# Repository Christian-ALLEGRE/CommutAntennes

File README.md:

# CommutAntennes
Antennas switcher using RPIPico and TFT 2"8 TouchScreen

V1.2 : 
  - The TFT 2"8 TouchScreen uses parallel 8 bits communication with RpiPico
  - PCB was manufactured by JLCPcb using Kicad/Ampli144MHz.zip (2023/09/14)
  - RpiPico Program V1.2 UI was design to manage :
    - The antenna switcher : 2 coax relay (HF and VHF)
    - A futur 144MHz 500W Power amplifier (not yet build at this time)
  
Updated on 29/12/2023 : 
  - The source code is now compatible with PlatformIO
    - CommutAntenneRpiPico-V1.2a.ino becomes src/main.cpp
    - The requested libraries were put in lib directory
    - a few lines where commented in GFX_Library_for_Arduino and TouchScreenOnRpPico
      to allow those libraries to compile (search for// F4LAA comment to find them)

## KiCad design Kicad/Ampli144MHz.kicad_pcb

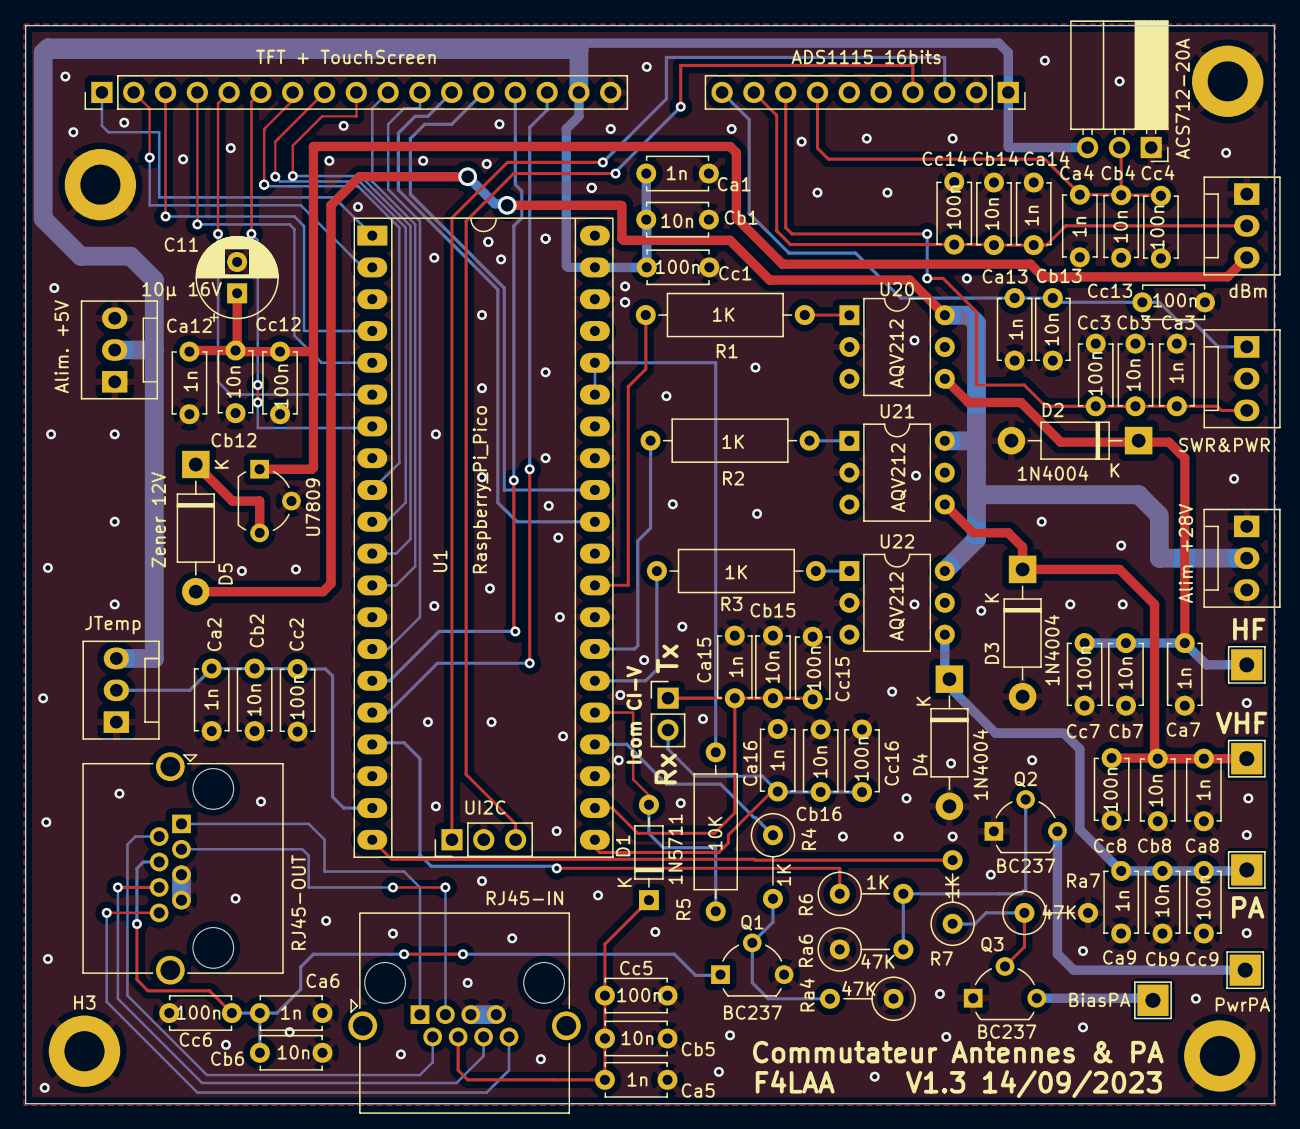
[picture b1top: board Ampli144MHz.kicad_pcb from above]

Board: 2 copper layers, 99.7 x 86.1 mm, 87 parts (0 on the bottom side), 37 nets.

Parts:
Alim +28V: Alim28V; FanPinHeader_1x03_P2.54mm_Vertical
C11: 10µ 16V; CP_Radial_D6.3mm_P2.50mm
CK1: RELAY_K1; TestPoint_THTPad_2.5x2.5mm_Drill1.2mm
CK2: RELAY_K2; TestPoint_THTPad_2.5x2.5mm_Drill1.2mm
CK3: RELAY_K3; TestPoint_THTPad_2.5x2.5mm_Drill1.2mm
CK220V: Alim 48V PA; TestPoint_THTPad_2.5x2.5mm_Drill1.2mm
CKBias1: BiasPA; TestPoint_THTPad_2.5x2.5mm_Drill1.2mm
Ca1, Ca2, Ca3, Ca4, Ca5, Ca6, Ca7, Ca8, Ca9, Ca12, Ca13, Ca14, Ca15, Ca16: 1n; C_Disc_D4.7mm_W2.5mm_P5.00mm
Cb1, Cb2, Cb3, Cb4, Cb5, Cb6, Cb7, Cb8, Cb9, Cb12, Cb13, Cb14, Cb15, Cb16: 10n; C_Disc_D4.7mm_W2.5mm_P5.00mm
Cc1, Cc2, Cc3, Cc4, Cc5, Cc6, Cc7, Cc8, Cc9, Cc12, Cc13, Cc14, Cc15, Cc16: 100n; C_Disc_D4.7mm_W2.5mm_P5.00mm
D1: 1N5711; D_DO-35_SOD27_P7.62mm_Horizontal
D2, D3, D4: 1N4004; D_DO-41_SOD81_P10.16mm_Horizontal
D5: Zener 12V; D_DO-41_SOD81_P10.16mm_Horizontal
H1, H2, H3, H4: MountingHole_Pad; MountingHole_3.2mm_M3_ISO7380_Pad
J5: Alim. +5V; FanPinHeader_1x03_P2.54mm_Vertical
JADC16bits: ADS1115 16bits; PinSocket_1x10_P2.54mm_Vertical
JAmp: ACS712-20A; PinSocket_1x03_P2.54mm_Horizontal
JCIV1: Icom CI-V; PinHeader_1x02_P2.54mm_Vertical
JS+P: SWR&PWR; FanPinHeader_1x03_P2.54mm_Vertical
JTFT+Touch: TFT + TouchScreen; PinHeader_1x17_P2.54mm_Vertical
JTemp: Temp; FanPinHeader_1x03_P2.54mm_Vertical
JdBm: dBm; FanPinHeader_1x03_P2.54mm_Vertical
Q1, Q2, Q3: BC237; TO-92L_Wide
R1, R2, R3: 1K; R_Axial_DIN0309_L9.0mm_D3.2mm_P12.70mm_Horizontal
R4, R6, R7: 1K; R_Axial_DIN0309_L9.0mm_D3.2mm_P5.08mm_Vertical
R5: 10K; R_Axial_DIN0309_L9.0mm_D3.2mm_P12.70mm_Horizontal
RJ45-IN, RJ45-OUT: RJ45_Amphenol_RJHSE5380
Ra4, Ra6, Ra7: 47K; R_Axial_DIN0309_L9.0mm_D3.2mm_P5.08mm_Vertical
U1: Raspberry_Pi_Pico; DIP-40_0.700in_Socket_LongPads
U20, U21, U22: AQV212; DIP-6_W7.62mm
U7809: LM78L09; TO-92L_Wide
UI2C: I2C; PinHeader_1x03_P2.54mm_Vertical

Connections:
+3.3V: R5.2, U1.35, U1.36
+5V: Ca1.2, Cb1.1, Cc1.2, J5.2, JADC16bits.1, JAmp.3, JTFT+Touch.16, JTemp.3, U1.39
+9V: C11.1, Ca12.1, Cb12.1, Cc12.1, JdBm.3, U7809.1 (VO)
+16V: D5.1 (K), U7809.3 (VI)
+28V: Alim +28V.2, U20.6, U21.6, U22.6
ADC0: JTFT+Touch.12, U1.31
ADC1: JTFT+Touch.13, U1.32
Amp: Ca4.1, Cb4.1, Cc4.1, JADC16bits.7, JAmp.2
BiasPAOff: R7.2, U1.20
CBiasPA: CKBias1.1, Q3.3 (E)
CK1: CK1.1, Ca7.1, Cb7.2, Cc7.2, D2.1 (K), U20.4
CK2: CK2.1, Ca8.1, Cb8.1, Cc8.2, D3.1 (K), U21.4
CK3: CK3.1, Ca9.2, Cb9.2, Cc9.2, D4.1 (K), U22.4
CK220V: CK220V.1, Q2.3 (E)
CPAOnOff: R6.1, U1.17
CPTTOut: Q1.2 (B), R4.1, R4.2, U1.24
GND: Alim +28V.1, Alim +28V.3, C11.2, Ca1.1, Ca2.2, Ca3.2, Ca4.2, Ca5.2, Ca6.2, Ca7.2, Ca8.2, Ca9.1, Ca12.2, Ca13.1, Ca14.2, Ca15.2, Ca16.2, Cb1.2, Cb2.1, Cb3.2, Cb4.2, Cb5.2, Cb6.2, Cb7.1, Cb8.2, Cb9.1, Cb12.2, Cb13.1, Cb14.2, Cb15.2, Cb16.2, Cc1.1, Cc2.1, Cc3.2, Cc4.2, Cc5.2, Cc6.2, Cc7.1, Cc8.1, Cc9.1, Cc12.2, Cc13.2, Cc14.2, Cc15.2, Cc16.2, D2.2 (A), D3.2 (A), D4.2 (A), H1.1, H2.1, H3.1, H4.1, J5.1, J5.3, JADC16bits.2, JAmp.1, JS+P.2, JTFT+Touch.17, JTemp.1, JdBm.1, Q1.3 (E), Q2.1 (C), Q3.1 (C), RJ45-IN.5, RJ45-IN.7, RJ45-OUT.5, RJ45-OUT.7, Ra4.1, Ra6.1, Ra7.2, U1.3, U1.8, U1.13, U1.18, U1.23, U1.28, U1.33, U1.38, U20.2, U21.2, U22.2, U7809.2 (GND), UI2C.2
unnamed: D1.2 (A), R5.1
unnamed: Q2.2 (B), R6.2, Ra6.2
unnamed: R1.1, U1.29
unnamed: R1.2, U20.1
unnamed: R2.1, U1.27
unnamed: R2.2, U21.1
unnamed: R3.1, U1.26
unnamed: R3.2, U22.1
PTT In: Ca5.1, Cb5.1, Cc5.1, D1.1 (K), RJ45-IN.4, U1.25
PTTOut: Ca6.1, Cb6.1, Cc6.1, Q1.1 (C), RJ45-OUT.4
PWR: Ca13.2, Cb13.2, Cc13.1, JADC16bits.10, JS+P.1
RX: Ca16.1, Cb16.1, Cc16.1, JCIV1.2, U1.21
SCL: JADC16bits.3, UI2C.1
SDA: JADC16bits.4, UI2C.3
SWR: Ca3.1, Cb3.1, Cc3.1, JADC16bits.8, JS+P.3
TX: Ca15.1, Cb15.1, Cc15.1, JCIV1.1, U1.22
T°: Ca2.1, Cb2.2, Cc2.2, JTemp.2, U1.19
XP: JTFT+Touch.14, U1.15
YM: JTFT+Touch.15, U1.16
dBm: Ca14.1, Cb14.1, Cc14.1, JADC16bits.9, JdBm.2

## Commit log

2023-12-29 new file: .gitignore new file: .vscode/extensions.json new file: Fao/Ampli144MHz-B_Cu.gbr new file: Fao/Ampli144MHz-B_Mask.gbr new file: Fao/Ampli144MHz-B_Paste.gbr new file: Fao/Ampli144MHz-B_Silksc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
2023-12-29 new file: lib/GFX_Library_for_Arduino/README.md new file: lib/GFX_Library_for_Arduino/examples/ArduinoVNC/ArduinoVNC.ino new file: lib/GFX_Library_for_Arduino/examples/ArduinoVNC/VNC_GFX.h new file: 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
2023-12-29 modified: README.md
2023-12-29 new file: images/20230911_130225.jpg new file: images/20230930_181311.jpg new file: images/20230930_235537.jpg new file: images/20231004_191355.jpg new file: images/20231006_193105.jpg new file: imag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
